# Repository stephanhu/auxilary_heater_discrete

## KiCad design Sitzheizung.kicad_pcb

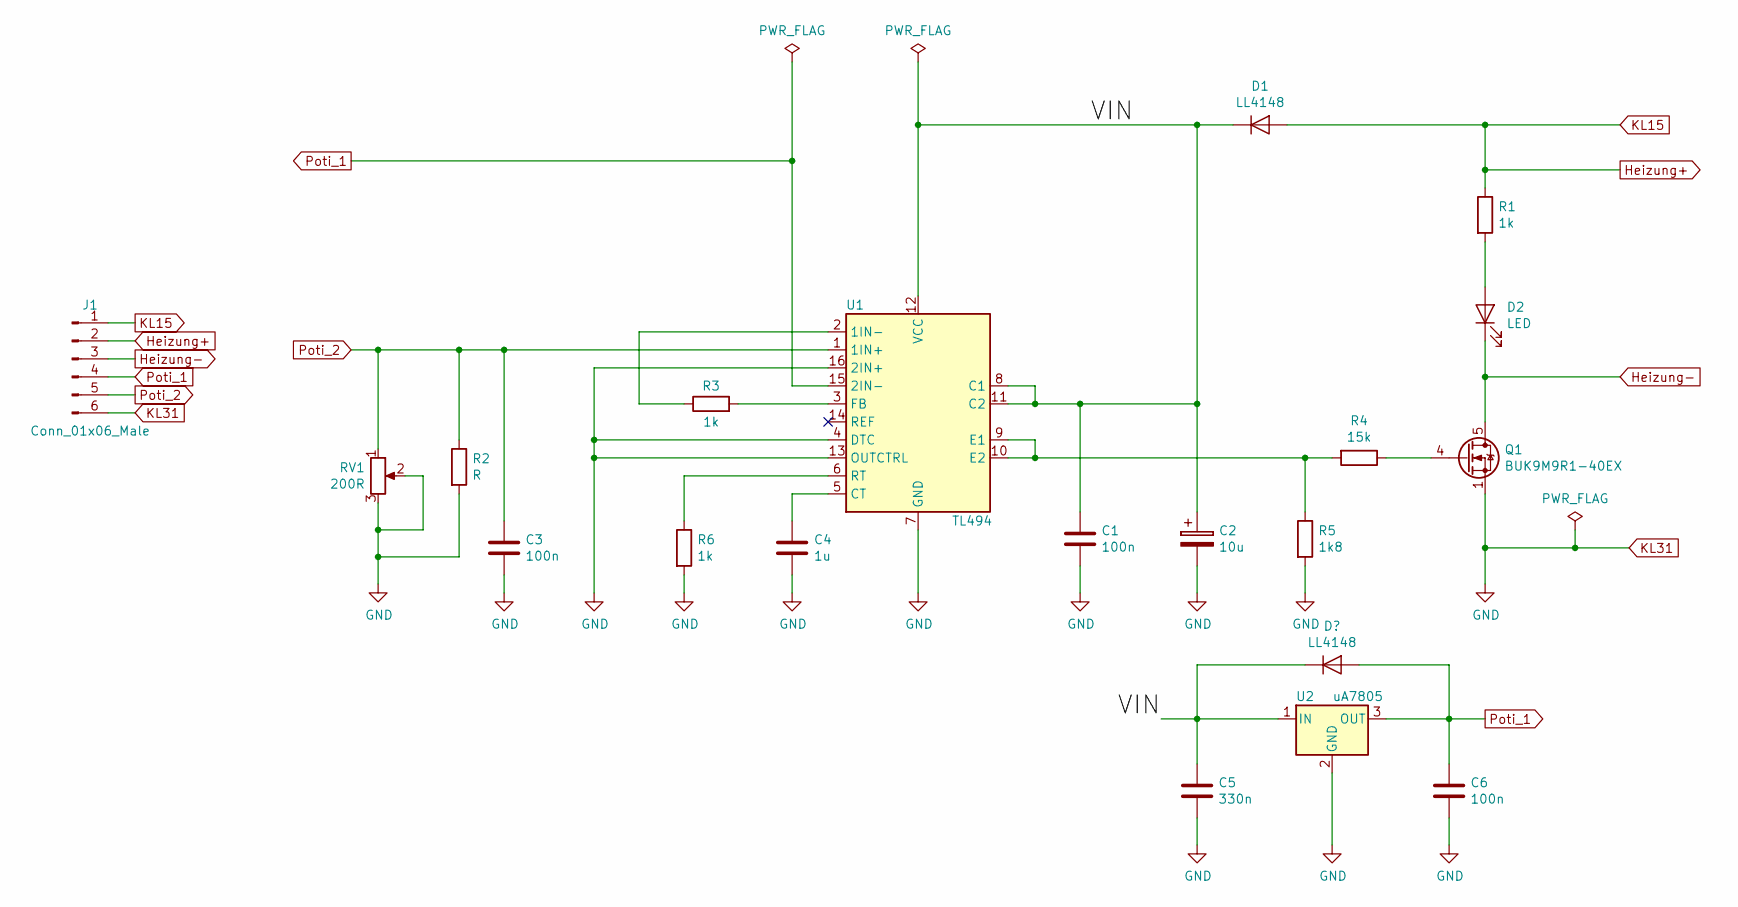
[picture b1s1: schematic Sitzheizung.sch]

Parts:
C1, C3, C6: 100n; C_0805_2012Metric_Pad1.15x1.40mm_HandSolder
C2: 10u; CP_Radial_D6.3mm_P2.50mm
C4: 1u; C_0805_2012Metric_Pad1.15x1.40mm_HandSolder
C5: 330n; C_0805_2012Metric_Pad1.15x1.40mm_HandSolder
D1: LL4148; D_MiniMELF
D2: LED; LED_0805_2012Metric_Pad0.98x1.40mm_HandSolder
J1: Conn_01x06_Male; TE_MQS_936287-2_1x06_P2.54mm_Horizontal
Q1: BUK9M9R1-40EX; LFPAK33
R1, R3, R6: 1k; R_0805_2012Metric_Pad1.15x1.40mm_HandSolder
R2: R; R_0805_2012Metric_Pad1.15x1.40mm_HandSolder
R4: 15k; R_0805_2012Metric_Pad1.15x1.40mm_HandSolder
R5: 1k8; R_0805_2012Metric_Pad1.15x1.40mm_HandSolder
RV1: 200R; Potentiometer_Bourns_3386X_Horizontal
U1: TL494; SOIC-16_3.9x9.9mm_P1.27mm
U2: uA7805; SOT-223-3_TabPin2

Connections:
/VIN: C1.1, C2.1, C5.1, D1.1 (K), U1.8 (C1), U1.11 (C2), U1.12 (VCC), U2.1 (IN); also elsewhere on the board
Heizung+: D1.2 (A), J1.1, J1.2, R1.1
Heizung-: D2.1 (K), J1.3, Q1.5 (D)
KL31: C1.2, C2.2, C3.2, C4.2, C5.2, C6.2, J1.6, Q1.1 (S), Q1.2 (S), Q1.3 (S), R2.2, R5.2, R6.2, RV1.2, RV1.3, U1.4 (DTC), U1.7 (GND), U1.13 (OUTCTRL), U1.16 (2IN+), U2.2 (GND)
unnamed: C4.1, U1.5 (CT)
unnamed: D2.2 (A), R1.2
unnamed: Q1.4 (G), R4.1
unnamed: R3.1, U1.2 (1IN-)
unnamed: R3.2, U1.3 (FB)
unnamed: R4.2, R5.1, U1.9 (E1), U1.10 (E2)
unnamed: R6.1, U1.6 (RT)
Poti_1: C6.1, J1.4, U1.15 (2IN-), U2.3 (OUT); also elsewhere on the board
Poti_2: C3.1, J1.5, R2.1, RV1.1, U1.1 (1IN+)

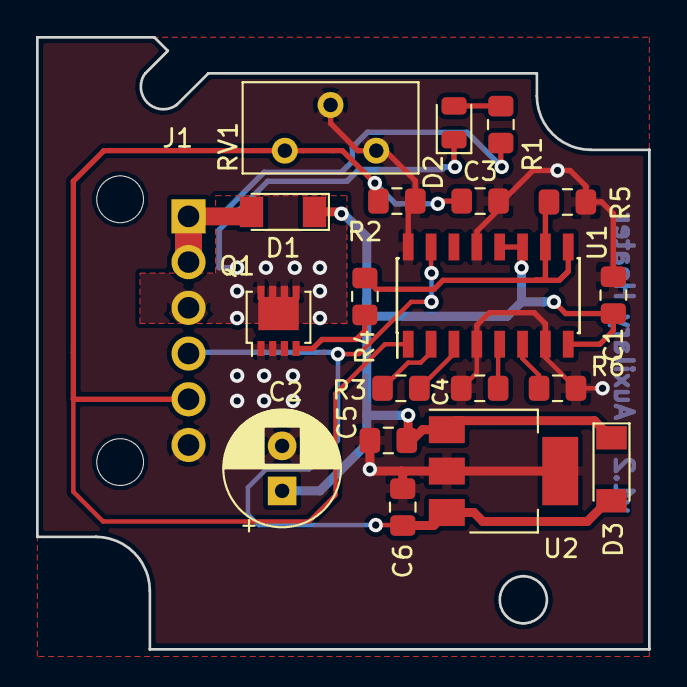
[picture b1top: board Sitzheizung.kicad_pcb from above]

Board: 2 copper layers, 34.0 x 34.0 mm, 20 parts (0 on the bottom side), 13 nets.

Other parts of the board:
D3: LL4148; D_MiniMELF

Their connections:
/VIN: D3.1; also elsewhere on the board
Poti_1: D3.2; also elsewhere on the board

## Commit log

2018-07-04 init
2018-07-04 started placement
2018-07-12 finished layout
2018-09-07 changed potentiometer
2019-02-27 added LDO
2019-02-27 missing annotation
2019-03-19 minor changes
